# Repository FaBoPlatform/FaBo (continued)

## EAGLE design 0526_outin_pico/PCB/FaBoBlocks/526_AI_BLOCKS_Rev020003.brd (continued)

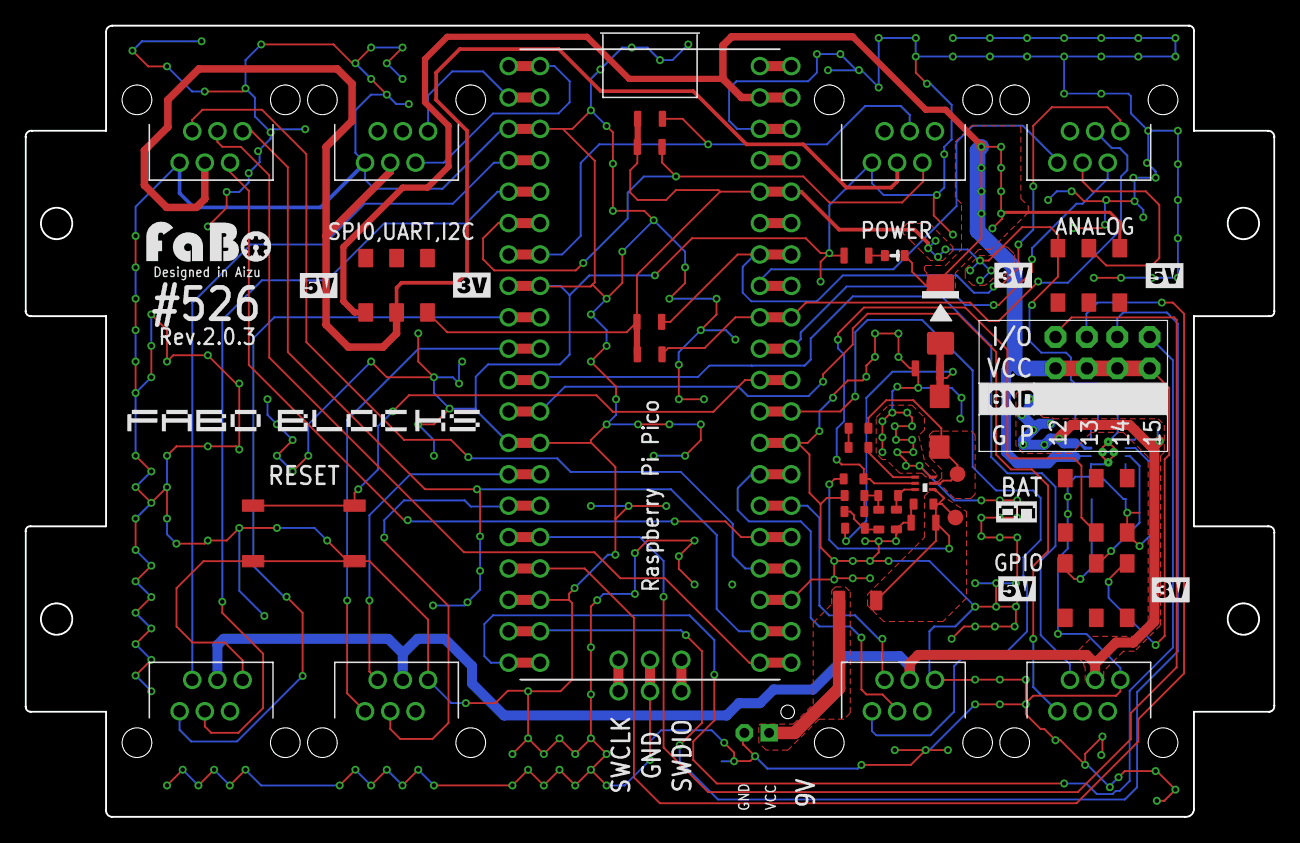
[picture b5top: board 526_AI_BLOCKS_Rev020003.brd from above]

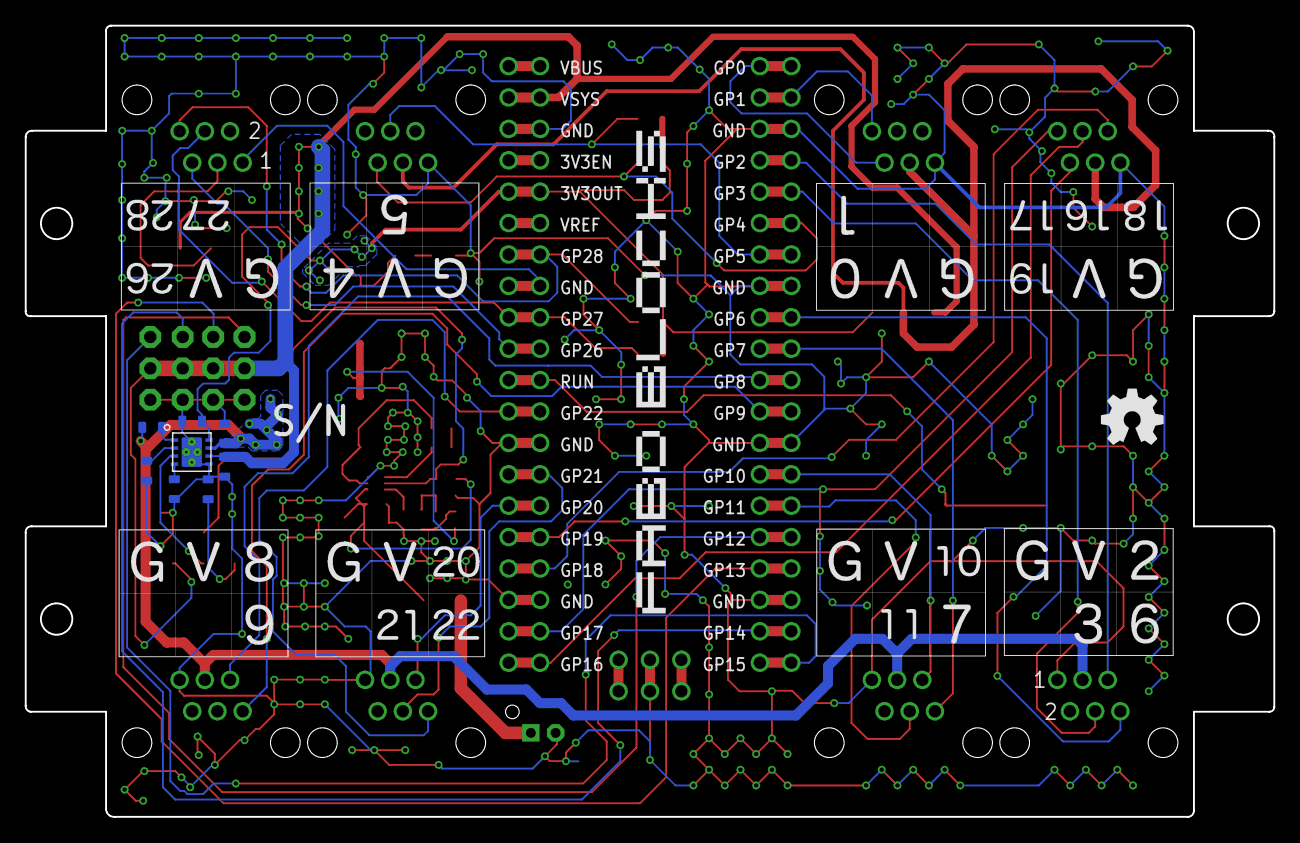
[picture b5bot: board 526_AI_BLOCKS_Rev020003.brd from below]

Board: 2 copper layers, 101.0 x 64.0 mm, 58 parts (8 on the bottom side), 55 nets.

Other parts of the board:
U$19: LOGO_SILK_GND
